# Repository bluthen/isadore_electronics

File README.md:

# isadore_electonics

Design files for the electronics of the Isadore Dryer Management System. Also included is what is called the MID software which queries the electronics and reports it back to the [isadore_server](https://github.com/bluthen/isadore_server/)

# Electronics Manufacture

Electronics manufactures usually want gerbers, centroid file, and a bill of materials. The latest pre-generated versions of these files can usually be found in the out directory (Example: `sensor_unitv3/out/`).

* The centroid and gerbers are in the zip file.
* The bill of materials is in the excel spreadsheet file (xlsx)
* An optional pins.png file may exist to show the manufacturer the location of pin1 for ICs.

Optionally you can generate the gerbers and centroid yourself depending by opening it up in [Eagle](https://www.autodesk.com/products/eagle/overview).

# Electronics Firmware

After you have a sensor unit or sensor hub, you need to program their firmware. To do this you need a AVR ISP programmer. Then there are script to help you program them. `sensor_unitv3/code/make.py`, `sensor_hubv3/code/Makefile`, and `fuse_crystal_clock.sh`.

*Note* you need a 5 pin ISP programmer. Most sold are 10 pin, so an adapter is needed.

To program the units or hubs you need some software installed:

* `avrdude`
* `gcc-avr`
* `avr-libc`

## Sensor Unit
A sensor unit can be programmed in many ways depending on what sensor modules you are going to plug into it.

Here is the help usage for `make.py`

```
Usage: make.py [OPTIONS] ADDRESS
  -h, --help                      Show this screen
  -d, --debug                     Debug build
  -p, --program                   Program unit
  -c, --clean                     Clean
  -f, --fuse                      Set fuse
  --prev303                       Build for prev3.03 unit
  --with-th                       Build with temperature humidty
  --with-pressurev1=m,b           Build in v1 pressure module
  --with-pressurev4a=cal_adjust   Build in v4a pressure module
  --with-pressurev4b=cal_adjust   Build in v4b pressure module
  --with-pressurev5=m,b           Build in v5 pressure module
  --with-anemometer               Build in Anemometer module
  --with-thermo                   Build in thermocouple module
  --with-multit                   Build in Multipoint-temp module
  --with-tach                     Build in tachometer module
```

So for example you might do with a unit, with the programmed placed and the unit powered.
```
python2 make.py -f -c -p --with-pressurev4b=0 102
```

If successful It is now programmed to use the pressurev4 module that gives you pressure/temperature/rh, and responses when address `102` is queried.

## Sensor Hub

To program the hub you would run with the programmer in place and powered:
```
cd sensor_hubv3/code
./fuse_crystal_clock.sh && make program
```

# MID (Master Interface Device)

This is basically the combination of a small computer (raspberry pi) and the hub electronics board. The hub and raspberry pi communicate serially. The hub has voltage regulators to power the raspberry pi.

## HUB<-> pi wiring

Notice for the power, Red is on TP1, and black is outside of usb connector.

Communication headers on pins 4 and 5 from outside corner.

## Install and configure raspbian

After installing raspian you'll want to set to enable access to the serail port with `raspi-config` and [disable the use of console by uart](https://www.raspberrypi.org/documentation/configuration/uart.md).

```
$ raspi-config
Interface Options->Serial->No->Yes
```

You'll also want to make sure the following are installed:

```
apt-get install python python-pip python-dev
pip install flask pytz requests restkit pyserial pymodbus numpy termcolor netifaces netaddr
```

## Troubleshooting
There is a script called `midsim.py` that can aid in troubleshooting. It allows you to query sensors from the command line. It is located at `sensor_hubv3/code/test/midsim.py` 

Below is the usage:

```
Usage: midsim.py [OPTION]...
  -h, --help            show this screen
  -v, --verbose         output verbose debug output
  -c, --continous=t,c   Keep pulling every t seconds, c many times c=0 for infinite
                        default is to pull once.
  -f, --format=format   The output format to use:
                        default:   The default style output
                        csv:       csv style output
  -t, --type=TYPE       TYPE=(temphum|anemometer|tachometer|thermocouple|pressure|pressurewide|
                              multipointreset|multipointc[1-4]|multipointaddrc[1-4]|ping|
                              unitversion|hubversion) *Required
  --get-cal             Get calibration value for type
  --set-cal=CAL_VALUE   Set calibration value for type
  -p, --port=PORT       PORT=#
  -a, --address=ADDRESS ADDRESS=#,#,#,...
  -u                    use udp instead of serial
  -d, --device=PATH     serial device to use for version 3, default /dev/ttyAMA0
  -o                    Use direct command code instead of general (aka version2)
  -j                    Just send commands then exit immediatly
  -s, --server=IP:PORT  Start midsim server listening on IP:PORT
  -r, --remote=IP:PORT  Query remote midsim server on IP:PORT

  address,port required except for --type=ping
  Max number of addresses is 32.
```

## Calibration
The main goal of the pressure modules was to report differencial pressure. The pressure module can be calibrated and there is a script to help with that process. It takes a large amounts of samples and sets an offset to match the reference. This script can be found at `sensor_hubv3/code/test/calibrator.py`

## Configure mid_software

Copy the mid_software to the raspberry pi. Copy `MID.cfg.example` to `MID.cfg` but one directory down from the location of mid_software. Modify MID.cfg for your needs. The most importanted are `baseurl` and `MIDpassword`Below is a reference for what each key means:

* `baseurl` The url to the base location of your running instance of [isadore_server](https://github.com/bluthen/isadore_server/).
* `MIDname` If you have multiple mids, this needs to be set so it knows which config to fetch. If it doesn't exist, all configs are fetched.
* `MIDpassword` The mid password that was set for your instance of isadore_server.
* `configpath` relative url where it should get the systems unit configuration. shouldn't need changing.
* `uploadpath` the relative url it should use to upload sensor data it gets. shouldn't need changing.
* `rcstatuspath` the relative url it uses for controls. shouldn't need changing.
* `hub_serial` the serial port to use to communicate with the hub electronics board. `/dev/ttyAMA0` on old raspberry pi's, `/dev/serial0` on new ones.
* `STORE_RAW_DATA_MODE` shouldn't need changing
* `RAW_DATA_LOC` shouldn't need changing
* `RS485_TIMEOUT` time out per unit. shouldn't need changing
* `RS485_BAUD` The serial baud rate to use. shouldn't need changing
* `enableRC_p` shouldn't need changing
* `mid_reading_interval_seconds` The minimal amount of time to pass before reading sensor data again.
* `log_level` The level to log at, can be `ERROR`, `WARNING`, or `DEBUG`
* `turn_off` If it should be not be activly getting readings and uploading them.

There are also some other configurations for specific temperature controls. For now for those parameters, please see the code to find them.

## Running mid_software

Put the following in the crontab of the user that is going to run mid_software on the MID. Replace the path to where you copied mid_software.

```
*/15 * * * * /home/pi/mid_software/processCheck.sh
*/10 * * * * /home/pi/mid_software/mid_log_check.sh
```

* `processCheck.sh` will start the process if it doesn't find it running.
* `mid_log_check.sh` tries to detect if the process locked up and will restart it, if it thinks it has.

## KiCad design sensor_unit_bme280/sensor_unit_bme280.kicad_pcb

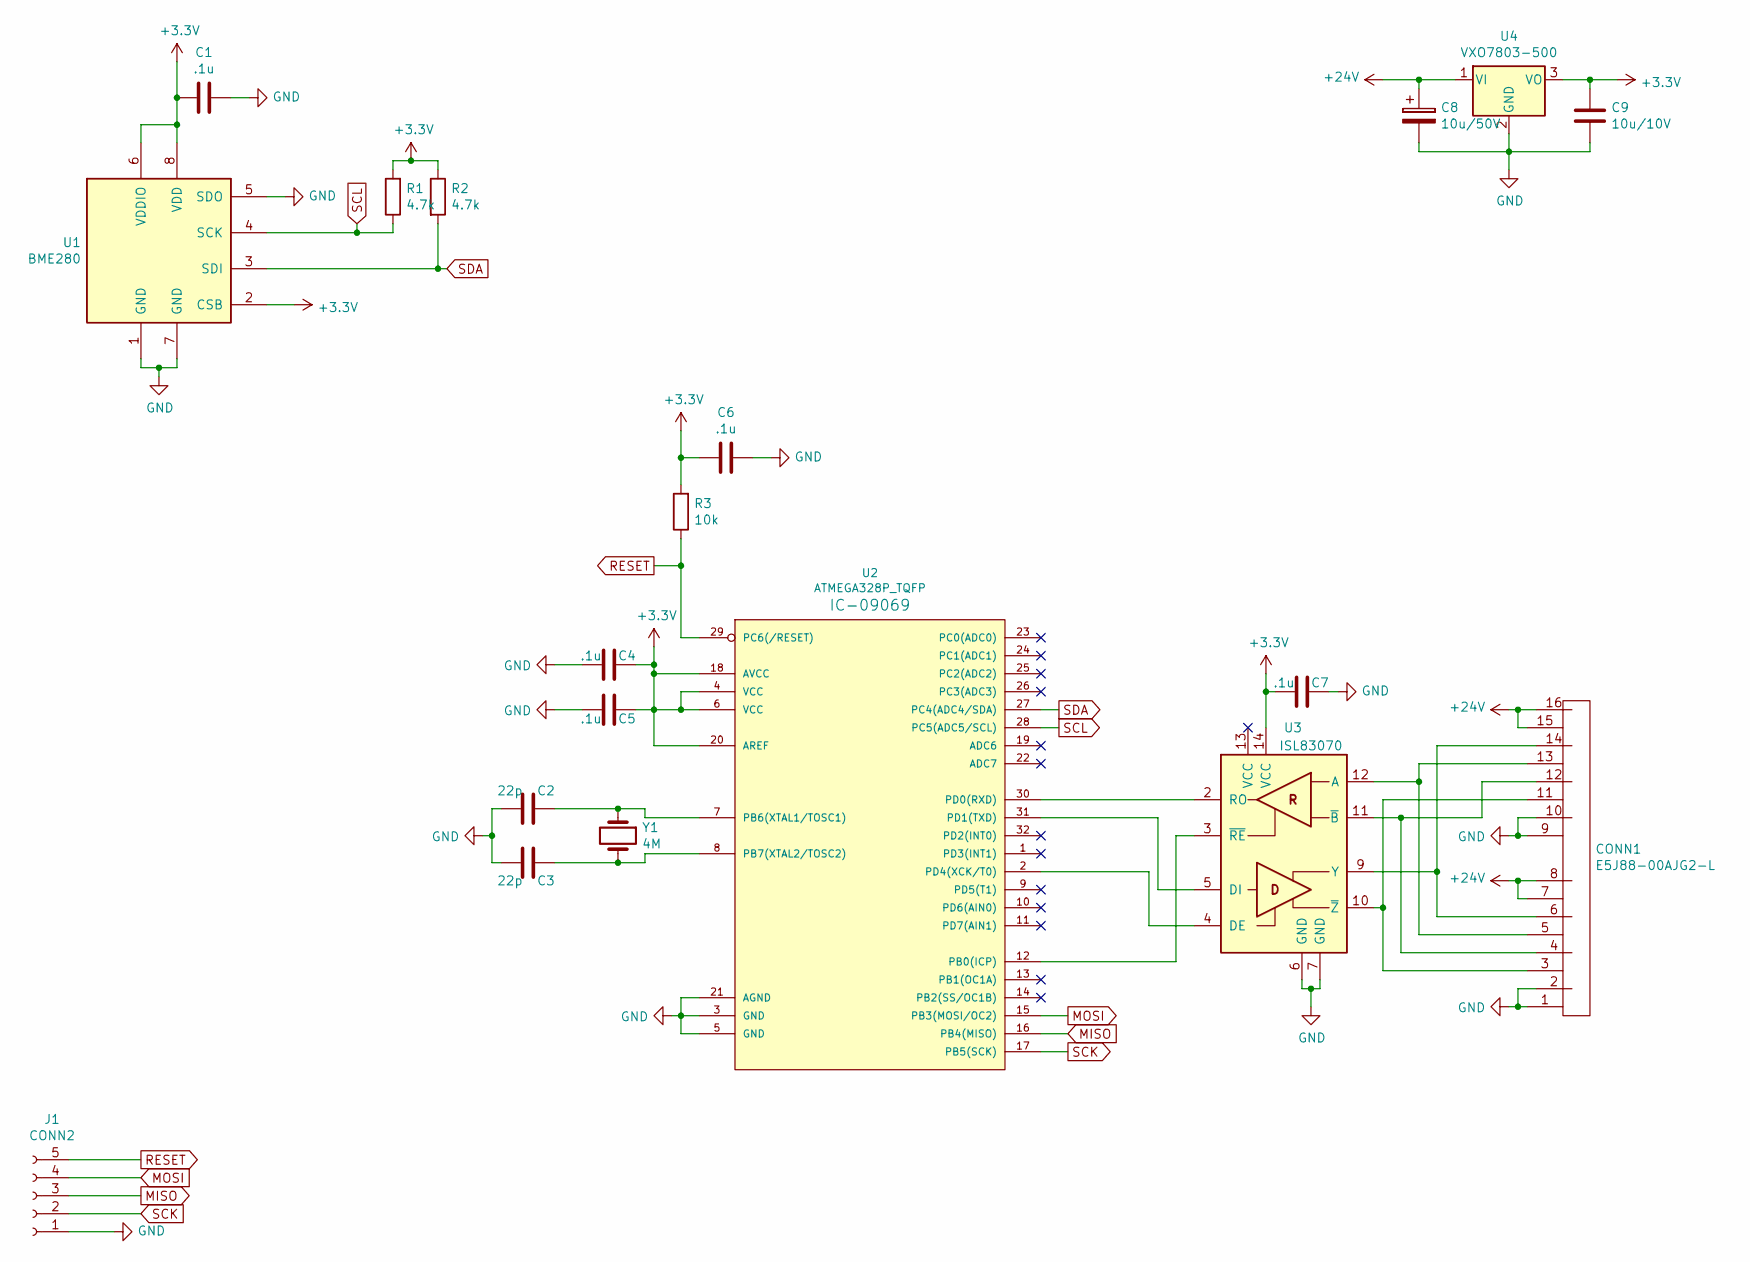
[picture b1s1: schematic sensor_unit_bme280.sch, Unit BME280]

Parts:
C1, C4, C5, C6, C7: .1u; 0603
C2, C3: 22p; 0603
C8: 10u/50V; CP_Elec_5x5.3
C9: 10u/10V; 0603
CONN1: E5J88-00AJG2-L
J1: CONN2; 1X05_LOCK_LONGPADS
R1, R2: 4.7k; 0603
R3: 10k; 0603
U1: BME280
U2: ATMEGA328P_TQFP; TQFP32-08
U3: ISL83070; SOIC-14_3.9x8.7mm_Pitch1.27mm
U4: VXO7803-500; 1X03_LOCK_LONGPADS
Y1: 4M; Crystal_SMD_HC49-SD

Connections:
+3V3: C1.2, C4.1, C5.1, C6.1, C7.2, C9.1, R1.2, R2.1, R3.2, U1.2 (CSB), U1.6 (VDDIO), U1.8 (VDD), U2.4 (VCC), U2.6 (VCC), U2.18 (AVCC), U2.20 (AREF), U3.14 (VCC), U4.3 (VO)
+24V: C8.1, CONN1.7, CONN1.8, CONN1.15, CONN1.16, U4.1 (VI)
GND: C1.1, C2.2, C3.2, C4.2, C5.2, C6.2, C7.1, C8.2, C9.2, CONN1.1, CONN1.2, CONN1.9, CONN1.10, J1.1, U1.1 (GND), U1.5 (SDO), U1.7 (GND), U2.3 (GND), U2.5 (GND), U2.21 (AGND), U3.6 (GND), U3.7 (GND), U4.2 (GND)
MISO: J1.3, U2.16 (PB4(MISO))
MOSI: J1.4, U2.15 (PB3(MOSI/OC2))
unnamed: C2.1, U2.7 (PB6(XTAL1/TOSC1)), Y1.1
unnamed: C3.1, U2.8 (PB7(XTAL2/TOSC2)), Y1.2
unnamed: CONN1.3, CONN1.11, U3.10 (~Z~)
unnamed: CONN1.4, CONN1.12, U3.11 (~B)
unnamed: CONN1.5, CONN1.13, U3.12 (A)
unnamed: CONN1.6, CONN1.14, U3.9 (Y)
unnamed: U2.2 (PD4(XCK/T0)), U3.4 (DE)
unnamed: U2.12 (PB0(ICP)), U3.3 (~RE)
unnamed: U2.30 (PD0(RXD)), U3.2 (RO)
unnamed: U2.31 (PD1(TXD)), U3.5 (DI)
RESET: J1.5, R3.1, U2.29 (PC6(/RESET))
SCK: J1.2, U2.17 (PB5(SCK))
SCL: R1.1, U1.4 (SCK), U2.28 (PC5(ADC5/SCL))
SDA: R2.2, U1.3 (SDI), U2.27 (PC4(ADC4/SDA))

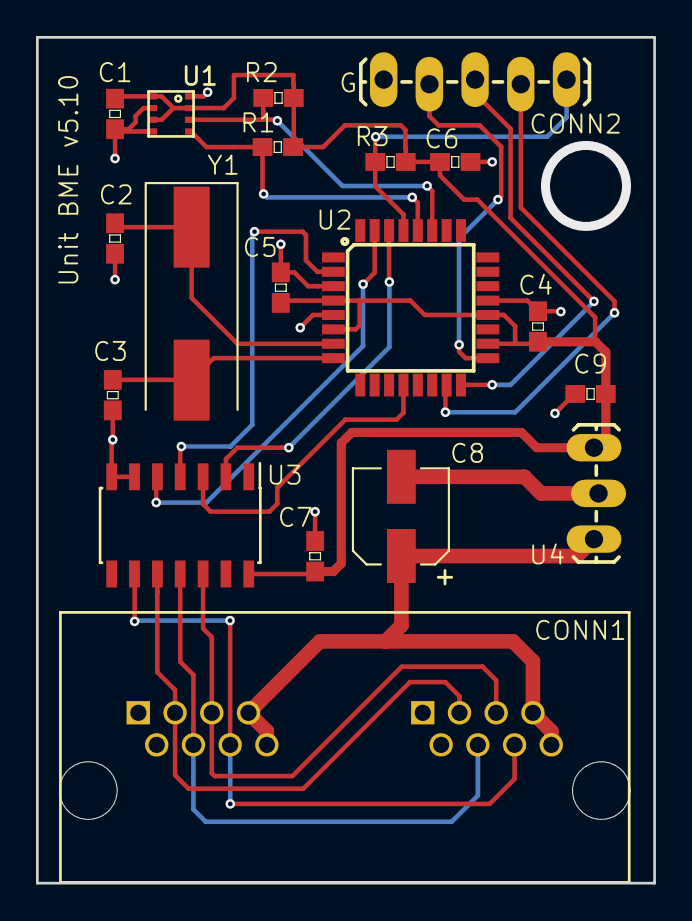
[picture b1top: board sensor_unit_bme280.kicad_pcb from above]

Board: 2 copper layers, 34.3 x 47.0 mm, 19 parts (0 on the bottom side), 19 nets.

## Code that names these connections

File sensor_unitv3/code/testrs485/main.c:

#define BAUD 9600

#include <stdio.h>
#include <avr/io.h>
#include <avr/interrupt.h>
#include <util/delay.h>
#include <util/setbaud.h>
#include <util/crc16.h>

#include "softuart.h"

#define RS485RE PB0
#define RS485REPORT PORTB
#define RS485REDDR DDRB
#define RS485DE PD4
#define RS485DEPORT PORTD
#define RS485DEDDR DDRD

static void ioinit(void);
static int uart_putchar(char c, FILE *stream);
static uint8_t uart_getchar(void);
static int swuart_putchar( char c, FILE *stream );
static FILE mystdout = FDEV_SETUP_STREAM(uart_putchar, NULL, _FDEV_SETUP_WRITE);
static FILE suart_stream = FDEV_SETUP_STREAM(swuart_putchar, NULL, _FDEV_SETUP_WRITE );

int main(void)
{
	uint16_t time = 0;
	uint16_t count = 0;
	unsigned char c = 0;
	ioinit();
	fprintf(stderr, "Unit rs485 test listening on rs485...\r\n");
	//DEBUG
	//turn on to rs485
	RS485DEPORT |=_BV(RS485DE); //DE is enabled when high
	fprintf(stderr, "DE on\r\n");
	while(1)
	{

		while (UCSR0A & (1<< RXC0))
		{
			c=UDR0;
			fprintf(stderr, "R: %c\r\n", c);
		}
		if(time >= 50000)
		{
			fprintf(stderr, "UC: %d\r\n", count);
			fprintf(stdout, "UC: %d\r\n", count);
			time=0;
			count++;
		}
		_delay_us(100);
		time++;
	}
}

void ioinit(void)
{
	softuart_init();
	sei(); //enable interupts
	DDRD &=~_BV(PD0); // read on usart RX pin
	DDRD |=_BV(PD1); // output on usart TX pin
	UBRR0H = UBRRH_VALUE;
	UBRR0L = UBRRL_VALUE;
	//UCSR0B = (1 << RXEN0)|(1<<TXEN0)|(1<<RXCIE0);
	UCSR0B = (1 << RXEN0)|(1<<TXEN0);
	stdout = &mystdout;
	stderr = &suart_stream;
	//Set RE and DE to outputs
	RS485REDDR |= _BV(RS485RE);
	RS485DEDDR |= _BV(RS485DE);
	//Enable RE, disable DE
	RS485REPORT &=~_BV(RS485RE); //RE is enabled when low
	RS485DEPORT &=~_BV(RS485DE); //DE is disabled when low
}


/*
 * Get character from serial
 */
uint8_t uart_getchar(void)
{
	while( !(UCSR0A & (1<<RXC0)) );
	return(UDR0);
}


/*
 * Send character to serial
 */
static int uart_putchar(char c, FILE *stream)
{
	//if (c == '\n') uart_putchar('\r', stream);

	loop_until_bit_is_set(UCSR0A, UDRE0);
	UDR0 = c;

	return 0;
}



// interface between avr-libc stdio and the modified Fleury uart-lib:
static int swuart_putchar( char c, FILE *stream )
{
	if ( c == '\n' ) {
		softuart_putchar( '\r' );
	}
	softuart_putchar( c );

	return 0;
}

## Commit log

2019-08-26 Added more instructions to the README.md
2019-08-26 more README.md instructions
2019-08-26 Added some mid_software documentation.
2020-08-10 Sensor unit bme 5.10. A cheaper T/RH/P sensor unit backward compatible
2020-08-11 Updated assembly bom, and pictures.
2021-06-27 Supports using PB5(SCK) as anemometer pin with software debounce as alternative to module.
2023-07-21 Added raw data protocol pdf
2023-07-21 MID(HUB) <-> Unit Pinout diagram
